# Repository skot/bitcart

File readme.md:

## The Bitcart

The bitcart is an open source controlboard for Bitmain Antminers. It runs off a RPi CM4 and the design is based around the [Raspberry Pi Compute Module 4 IO Board](https://www.raspberrypi.com/products/compute-module-4-io-board/)

If you are trying run a Bitcoin ASIC miner somewhere besides a datacenter, this is the controlboard for you.

**design is currently in alpha stage and untested!**

### Goals
- Initial support for Antminer S19J, S19K and S19XP series miners.
  - eventual support for S19, S17 and S9 legacy miners. 
- Fully open source hardware and firmware
- Runs the open source [esp-miner](http://github.com/skot/esp-miner) ported to linux.
  - miner FW modularized to allow for easy modification. Better utilize stranded energy! 
- IO options for customization
  - Ethernet
  - WiFi
  - Bluetooth
  - USB2
  - PCIe
  - RPi 40-pin header
- Built-in options for hashboard testing and repair

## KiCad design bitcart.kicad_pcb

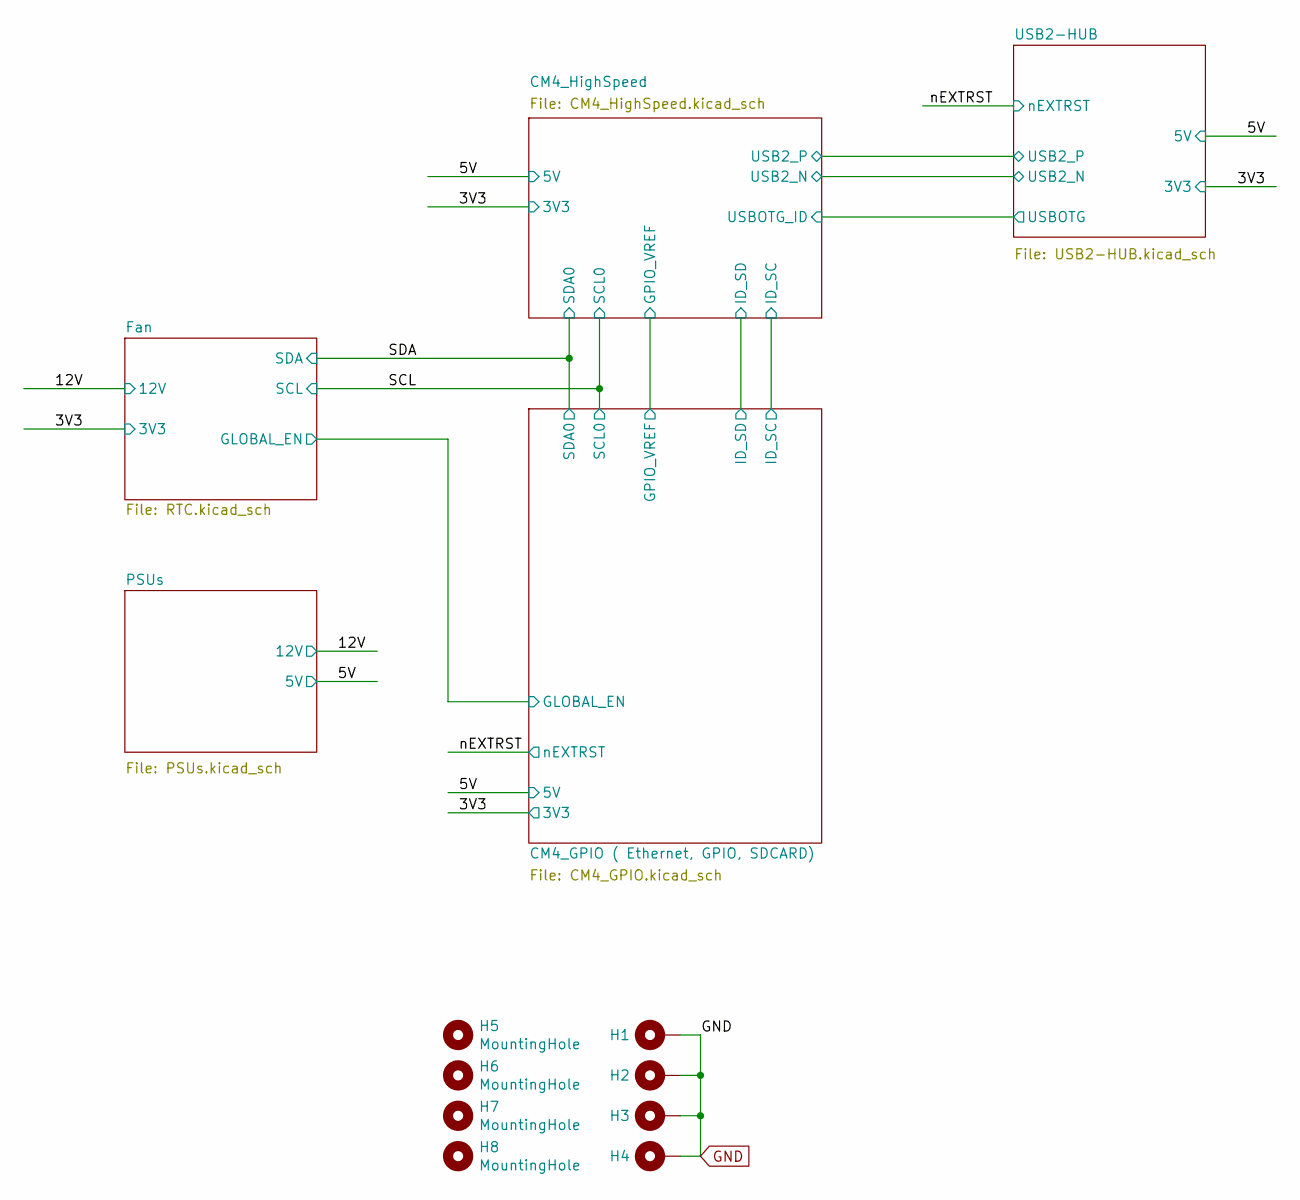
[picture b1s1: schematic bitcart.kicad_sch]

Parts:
H1, H2, H3, H4: MountingHole_Pad; MountingHole_3mm_Pad
H5, H6, H7, H8: MountingHole; MountingHole_2.7mm_M2.5; Part Description M2.5 mounting hole

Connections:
GND: H1.1, H2.1, H3.1, H4.1; also elsewhere on the board

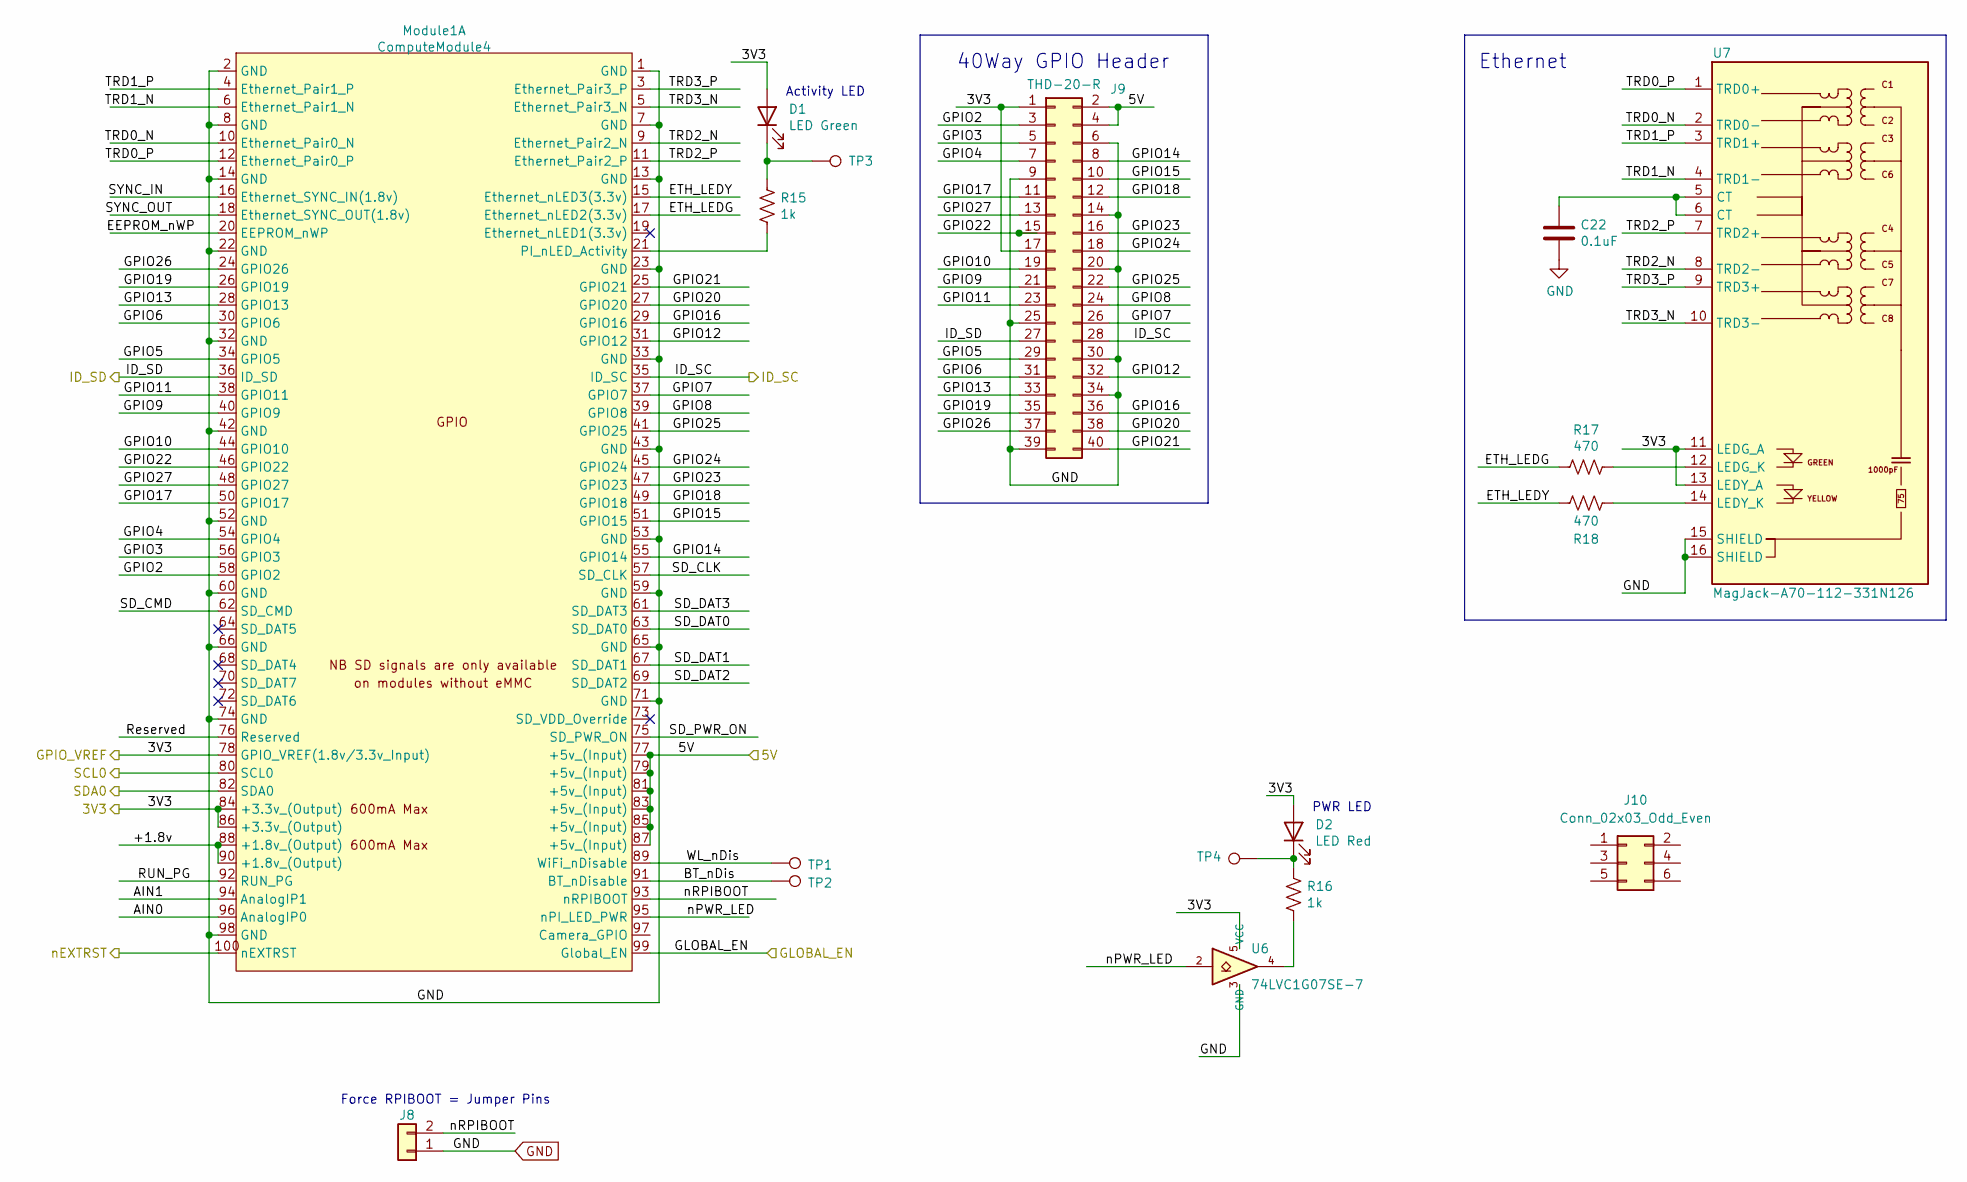
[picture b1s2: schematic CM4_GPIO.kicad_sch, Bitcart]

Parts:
C22: 0.1uF; C_0402_1005Metric; PARTNO KGM05AR71C104KH
D1: LED Green; LED_0603_1608Metric; PARTNO LTST-S270KGKT
D2: LED Red; LED_0603_1608Metric; Part Description Red 620nm LED Indication - Discrete 2.2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
J8: Conn_01x02; PinHeader_1x02_P2.54mm_Vertical
J9: THD-20-R; PinHeader_2x20_P2.54mm_Vertical; Part Description PinHeader_2x20_P2.54mm_Vertical
J10: Conn_02x03_Odd_Even; CONN-TH_6P-P2.00_PHD-2X3A
Module1: ComputeModule4; Raspberry-Pi-4-Compute-Module; PARTNO DF40C-100DS-0.4V(58)
R15, R16: 1k; R_0402_1005Metric; Part Description Resistor 1K M1005 1% 63mW
R17, R18: 470; R_0402_1005Metric; Part Description Resistor 470R M1005 1% 63mW
TP1, TP2, TP3, TP4: TestPoint; TestPoint_Pad_D1.5mm
U6: 74LVC1G07SE-7; SOT-353_SC-70-5; PARTNO 74LVC1G07GW,125
U7: MagJack-A70-112-331N126; ARJM11D7-502-AB-EW2_ABR; Part Description Gigabit Ethernet Magjack

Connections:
/3V3: D1.2 (A), D2.2 (A), J9.1, J9.17, Module1.78 (GPIO_VREF(1.8v/3.3v_Input)), Module1.84 (+3.3v_(Output)), Module1.86 (+3.3v_(Output)), U6.5 (VCC), U7.11 (LEDG_A), U7.13 (LEDY_A); also elsewhere on the board
/5V: J9.2, J9.4, Module1.77 (+5v_(Input)), Module1.79 (+5v_(Input)), Module1.81 (+5v_(Input)), Module1.83 (+5v_(Input)), Module1.85 (+5v_(Input)), Module1.87 (+5v_(Input)); also elsewhere on the board
/CM4_GPIO ( Ethernet, GPIO, SDCARD)/+1.8v: Module1.88 (+1.8v_(Output)), Module1.90 (+1.8v_(Output))
/CM4_GPIO ( Ethernet, GPIO, SDCARD)/AIN0: Module1.96 (AnalogIP0)
/CM4_GPIO ( Ethernet, GPIO, SDCARD)/AIN1: Module1.94 (AnalogIP1)
/CM4_GPIO ( Ethernet, GPIO, SDCARD)/BT_nDis: Module1.91 (BT_nDisable), TP2.1
/CM4_GPIO ( Ethernet, GPIO, SDCARD)/EEPROM_nWP: Module1.20 (EEPROM_nWP)
/CM4_GPIO ( Ethernet, GPIO, SDCARD)/ETH_LEDG: Module1.17 (Ethernet_nLED2(3.3v)), R17.2
/CM4_GPIO ( Ethernet, GPIO, SDCARD)/ETH_LEDY: Module1.15 (Ethernet_nLED3(3.3v)), R18.2
/CM4_GPIO ( Ethernet, GPIO, SDCARD)/GLOBAL_EN: Module1.99 (Global_EN)
/CM4_GPIO ( Ethernet, GPIO, SDCARD)/GPIO2: J9.3, Module1.58 (GPIO2)
/CM4_GPIO ( Ethernet, GPIO, SDCARD)/GPIO3: J9.5, Module1.56 (GPIO3)
/CM4_GPIO ( Ethernet, GPIO, SDCARD)/GPIO4: J9.7, Module1.54 (GPIO4)
/CM4_GPIO ( Ethernet, GPIO, SDCARD)/GPIO5: J9.29, Module1.34 (GPIO5)
/CM4_GPIO ( Ethernet, GPIO, SDCARD)/GPIO6: J9.31, Module1.30 (GPIO6)
/CM4_GPIO ( Ethernet, GPIO, SDCARD)/GPIO7: J9.26, Module1.37 (GPIO7)
/CM4_GPIO ( Ethernet, GPIO, SDCARD)/GPIO8: J9.24, Module1.39 (GPIO8)
/CM4_GPIO ( Ethernet, GPIO, SDCARD)/GPIO9: J9.21, Module1.40 (GPIO9)
/CM4_GPIO ( Ethernet, GPIO, SDCARD)/GPIO10: J9.19, Module1.44 (GPIO10)
/CM4_GPIO ( Ethernet, GPIO, SDCARD)/GPIO11: J9.23, Module1.38 (GPIO11)
/CM4_GPIO ( Ethernet, GPIO, SDCARD)/GPIO12: J9.32, Module1.31 (GPIO12)
/CM4_GPIO ( Ethernet, GPIO, SDCARD)/GPIO13: J9.33, Module1.28 (GPIO13)
/CM4_GPIO ( Ethernet, GPIO, SDCARD)/GPIO14: J9.8, Module1.55 (GPIO14)
/CM4_GPIO ( Ethernet, GPIO, SDCARD)/GPIO15: J9.10, Module1.51 (GPIO15)
/CM4_GPIO ( Ethernet, GPIO, SDCARD)/GPIO16: J9.36, Module1.29 (GPIO16)
/CM4_GPIO ( Ethernet, GPIO, SDCARD)/GPIO17: J9.11, Module1.50 (GPIO17)
/CM4_GPIO ( Ethernet, GPIO, SDCARD)/GPIO18: J9.12, Module1.49 (GPIO18)
/CM4_GPIO ( Ethernet, GPIO, SDCARD)/GPIO19: J9.35, Module1.26 (GPIO19)
/CM4_GPIO ( Ethernet, GPIO, SDCARD)/GPIO20: J9.38, Module1.27 (GPIO20)
/CM4_GPIO ( Ethernet, GPIO, SDCARD)/GPIO21: J9.40, Module1.25 (GPIO21)
/CM4_GPIO ( Ethernet, GPIO, SDCARD)/GPIO22: J9.15, Module1.46 (GPIO22)
/CM4_GPIO ( Ethernet, GPIO, SDCARD)/GPIO23: J9.16, Module1.47 (GPIO23)
/CM4_GPIO ( Ethernet, GPIO, SDCARD)/GPIO24: J9.18, Module1.45 (GPIO24)
/CM4_GPIO ( Ethernet, GPIO, SDCARD)/GPIO25: J9.22, Module1.41 (GPIO25)
/CM4_GPIO ( Ethernet, GPIO, SDCARD)/GPIO26: J9.37, Module1.24 (GPIO26)
/CM4_GPIO ( Ethernet, GPIO, SDCARD)/GPIO27: J9.13, Module1.48 (GPIO27)
/CM4_GPIO ( Ethernet, GPIO, SDCARD)/ID_SC: J9.28, Module1.35 (ID_SC); also elsewhere on the board
/CM4_GPIO ( Ethernet, GPIO, SDCARD)/ID_SD: J9.27, Module1.36 (ID_SD); also elsewhere on the board
/CM4_GPIO ( Ethernet, GPIO, SDCARD)/RUN_PG: Module1.92 (RUN_PG)
/CM4_GPIO ( Ethernet, GPIO, SDCARD)/Reserved: Module1.76 (Reserved)
/CM4_GPIO ( Ethernet, GPIO, SDCARD)/SD_CLK: Module1.57 (SD_CLK)
/CM4_GPIO ( Ethernet, GPIO, SDCARD)/SD_CMD: Module1.62 (SD_CMD)
/CM4_GPIO ( Ethernet, GPIO, SDCARD)/SD_DAT0: Module1.63 (SD_DAT0)
/CM4_GPIO ( Ethernet, GPIO, SDCARD)/SD_DAT1: Module1.67 (SD_DAT1)
/CM4_GPIO ( Ethernet, GPIO, SDCARD)/SD_DAT2: Module1.69 (SD_DAT2)
/CM4_GPIO ( Ethernet, GPIO, SDCARD)/SD_DAT3: Module1.61 (SD_DAT3)
/CM4_GPIO ( Ethernet, GPIO, SDCARD)/SD_PWR_ON: Module1.75 (SD_PWR_ON)
/CM4_GPIO ( Ethernet, GPIO, SDCARD)/SYNC_IN: Module1.16 (Ethernet_SYNC_IN(1.8v))
/CM4_GPIO ( Ethernet, GPIO, SDCARD)/SYNC_OUT: Module1.18 (Ethernet_SYNC_OUT(1.8v))
/CM4_GPIO ( Ethernet, GPIO, SDCARD)/TRD0_N: Module1.10 (Ethernet_Pair0_N), U7.2 (TRD0-)
/CM4_GPIO ( Ethernet, GPIO, SDCARD)/TRD0_P: Module1.12 (Ethernet_Pair0_P), U7.1 (TRD0+)
/CM4_GPIO ( Ethernet, GPIO, SDCARD)/TRD1_N: Module1.6 (Ethernet_Pair1_N), U7.4 (TRD1-)
/CM4_GPIO ( Ethernet, GPIO, SDCARD)/TRD1_P: Module1.4 (Ethernet_Pair1_P), U7.3 (TRD1+)
/CM4_GPIO ( Ethernet, GPIO, SDCARD)/TRD2_N: Module1.9 (Ethernet_Pair2_N), U7.8 (TRD2-)
/CM4_GPIO ( Ethernet, GPIO, SDCARD)/TRD2_P: Module1.11 (Ethernet_Pair2_P), U7.7 (TRD2+)
/CM4_GPIO ( Ethernet, GPIO, SDCARD)/TRD3_N: Module1.5 (Ethernet_Pair3_N), U7.10 (TRD3-)
/CM4_GPIO ( Ethernet, GPIO, SDCARD)/TRD3_P: Module1.3 (Ethernet_Pair3_P), U7.9 (TRD3+)
/CM4_GPIO ( Ethernet, GPIO, SDCARD)/WL_nDis: Module1.89 (WiFi_nDisable), TP1.1
/CM4_GPIO ( Ethernet, GPIO, SDCARD)/nPWR_LED: Module1.95 (nPI_LED_PWR), U6.2
/CM4_GPIO ( Ethernet, GPIO, SDCARD)/nRPIBOOT: J8.2, Module1.93 (nRPIBOOT)
/SCL: Module1.80 (SCL0); also elsewhere on the board
/SDA: Module1.82 (SDA0); also elsewhere on the board
/nEXTRST: Module1.100 (nEXTRST); also elsewhere on the board
GND: C22.2, J8.1, J9.6, J9.9, J9.14, J9.20, J9.25, J9.30, J9.34, J9.39, Module1.1 (GND), Module1.2 (GND), Module1.7 (GND), Module1.8 (GND), Module1.13 (GND), Module1.14 (GND), Module1.22 (GND), Module1.23 (GND), Module1.32 (GND), Module1.33 (GND), Module1.42 (GND), Module1.43 (GND), Module1.52 (GND), Module1.53 (GND), Module1.59 (GND), Module1.60 (GND), Module1.65 (GND), Module1.66 (GND), Module1.71 (GND), Module1.74 (GND), Module1.98 (GND), U6.3 (GND), U7.15 (SHIELD), U7.16 (SHIELD); also elsewhere on the board
unnamed: C22.1, U7.5 (CT), U7.6 (CT)
unnamed: D1.1 (K), R15.1, TP3.1
unnamed: D2.1 (K), R16.1, TP4.1
unnamed: Module1.21 (PI_nLED_Activity), R15.2
unnamed: R16.2, U6.4
unnamed: R17.1, U7.12 (LEDG_K)
unnamed: R18.1, U7.14 (LEDY_K)

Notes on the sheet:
PWR LED
40Way GPIO Header
Ethernet
Activity LED
Force RPIBOOT = Jumper Pins

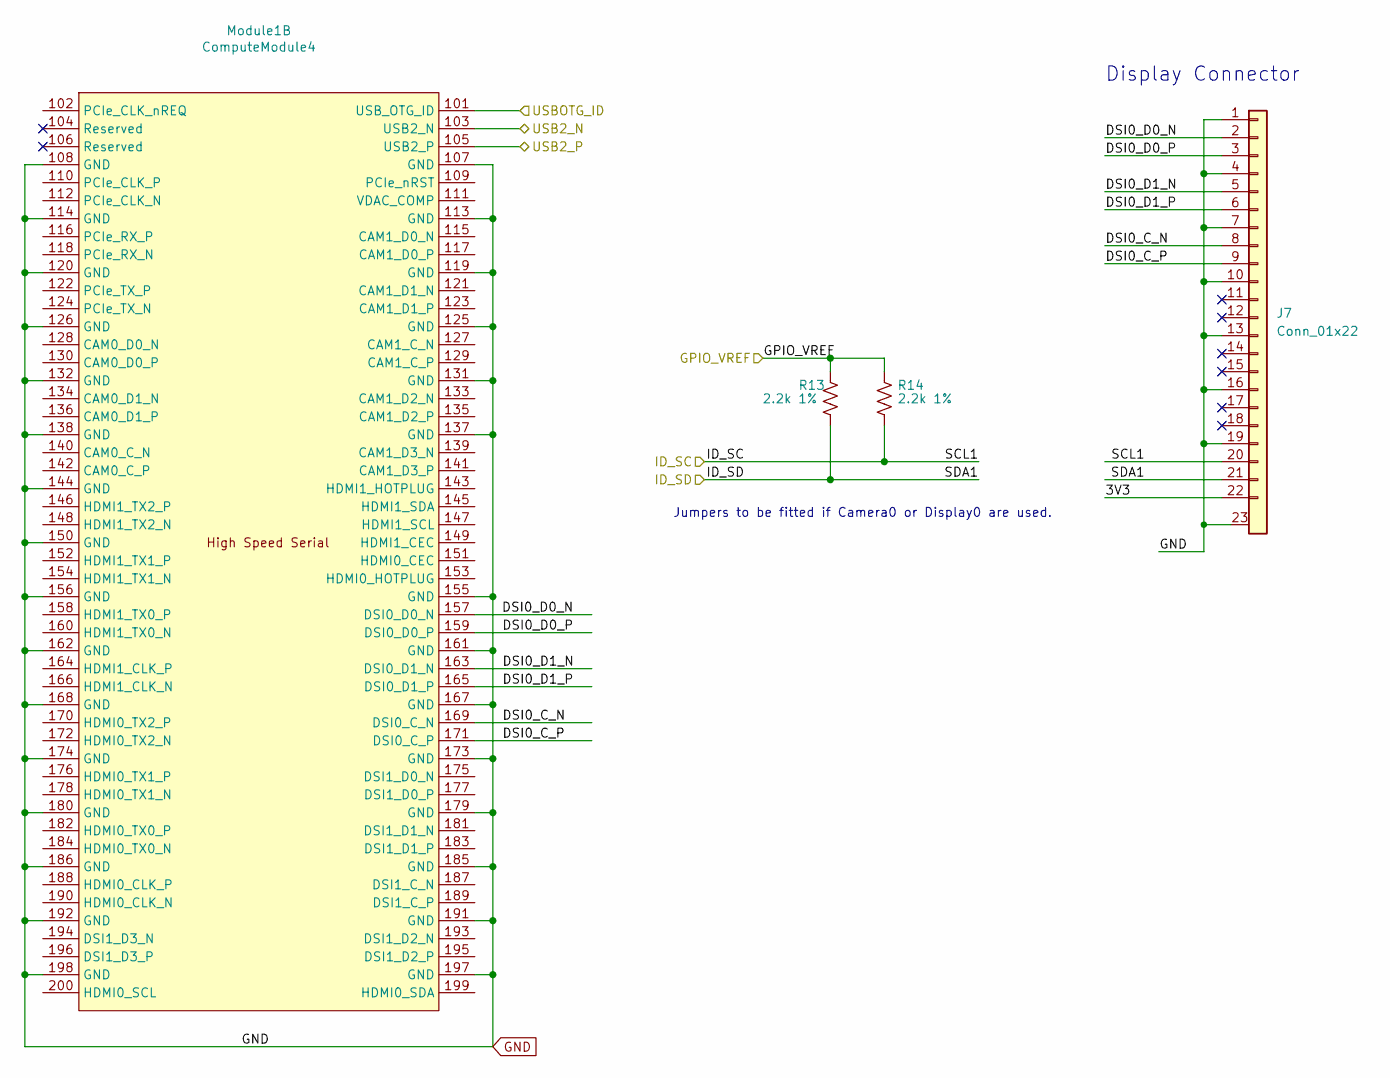
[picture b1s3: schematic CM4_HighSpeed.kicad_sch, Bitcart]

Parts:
J7: Conn_01x22; CON22_1X22_DUTB_HRS_HIR; PARTNO FH12-22S-0.5SVA(54)
Module1: ComputeModule4; Raspberry-Pi-4-Compute-Module; PARTNO DF40C-100DS-0.4V(58)
R13, R14: 2.2k 1%; R_0402_1005Metric; PARTNO RC0402FR-072K2L

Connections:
/3V3: R13.1, R14.1; also elsewhere on the board
/CM4_GPIO ( Ethernet, GPIO, SDCARD)/ID_SC: J7.20, R14.2; also elsewhere on the board
/CM4_GPIO ( Ethernet, GPIO, SDCARD)/ID_SD: J7.21, R13.2; also elsewhere on the board
/CM4_HighSpeed/3V3: J7.22
/CM4_HighSpeed/DSI0_C_N: J7.8, Module1.169 (DSI0_C_N)
/CM4_HighSpeed/DSI0_C_P: J7.9, Module1.171 (DSI0_C_P)
/CM4_HighSpeed/DSI0_D0_N: J7.2, Module1.157 (DSI0_D0_N)
/CM4_HighSpeed/DSI0_D0_P: J7.3, Module1.159 (DSI0_D0_P)
/CM4_HighSpeed/DSI0_D1_N: J7.5, Module1.163 (DSI0_D1_N)
/CM4_HighSpeed/DSI0_D1_P: J7.6, Module1.165 (DSI0_D1_P)
/CM4_HighSpeed/USB2_N: Module1.103 (USB2_N); also elsewhere on the board
/CM4_HighSpeed/USB2_P: Module1.105 (USB2_P); also elsewhere on the board
/CM4_HighSpeed/USBOTG_ID: Module1.101 (USB_OTG_ID); also elsewhere on the board
GND: J7.1, J7.4, J7.7, J7.10, J7.13, J7.16, J7.19, J7.23, J7.24, J7.25, J7.26, Module1.107 (GND), Module1.108 (GND), Module1.113 (GND), Module1.114 (GND), Module1.119 (GND), Module1.120 (GND), Module1.125 (GND), Module1.126 (GND), Module1.131 (GND), Module1.132 (GND), Module1.137 (GND), Module1.138 (GND), Module1.144 (GND), Module1.150 (GND), Module1.155 (GND), Module1.156 (GND), Module1.161 (GND), Module1.162 (GND), Module1.167 (GND), Module1.168 (GND), Module1.173 (GND), Module1.174 (GND), Module1.179 (GND), Module1.180 (GND), Module1.185 (GND), Module1.186 (GND), Module1.191 (GND), Module1.192 (GND), Module1.197 (GND), Module1.198 (GND); also elsewhere on the board

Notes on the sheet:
Jumpers to be fitted if Camera0 or Display0 are used.
Display Connector

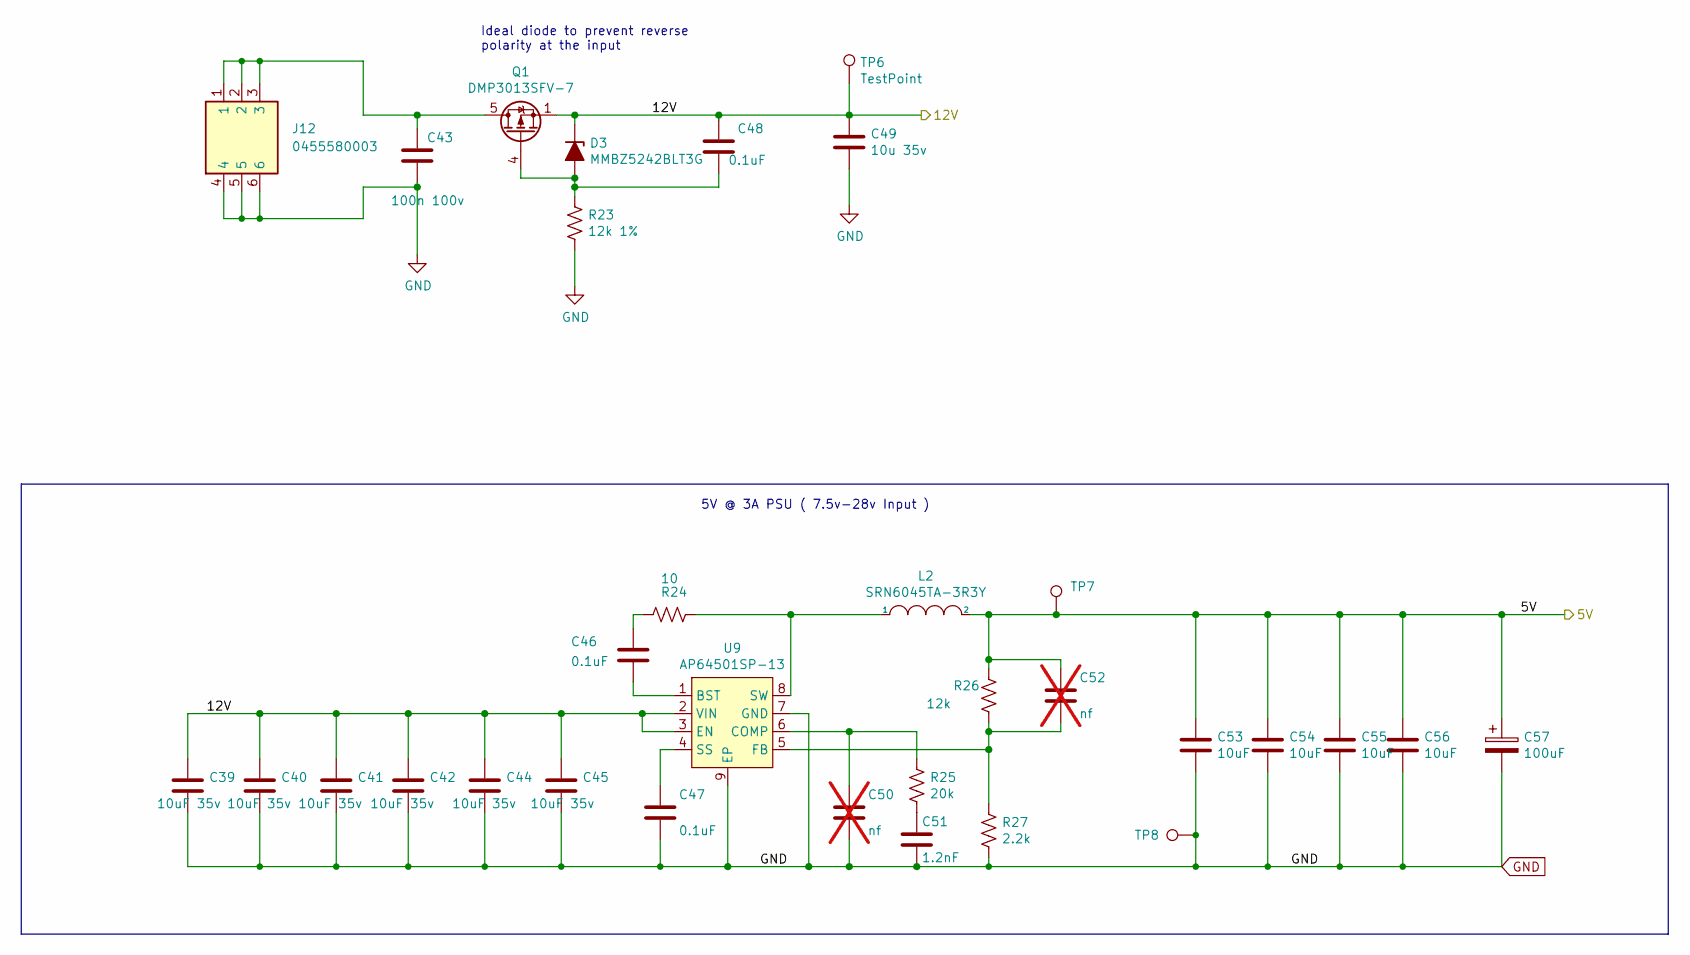
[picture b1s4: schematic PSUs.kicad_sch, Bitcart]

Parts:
C39, C40, C41, C42, C44, C45: 10uF 35v; C_0805_2012Metric; Part Description 10uF 10% or 20% 35V Ceramic Capacitor X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
C43: 100n 100v; C_0402_1005Metric; Part Description 0.1uF 10% 100V Ceramic Capacitor X5R 04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
C46, C47, C48: 0.1uF; C_0402_1005Metric; PARTNO KGM05AR71C104KH
C49: 10u 35v; C_0805_2012Metric; Part Description 10uF 10% or 20% 35V Ceramic Capacitor X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
C50: nf; C_0402_1005Metric; not fitted
C51: 1.2nF; C_0402_1005Metric; Part Description 1200pF 10% 10V Ceramic Capacitor X5R 04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
C52: nf; C_0402_1005Metric; Part Description 220 pF, 50 V, 0402 [1005 Metric], ± 5%,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; not fitted
C53, C54, C55, C56: 10uF; C_0805_2012Metric; Part Description 10uF 10% 10V Ceramic Capacitor X7R 0805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
C57: 100uF; CP_EIA-7343-31_Kemet-D; Part Description Capacitor, SP-Cap, 100u, 6.3V, 15mR ESR
D3: MMBZ5242BLT3G; D_SOT-23_ANK; PARTNO MMBZ5242BLT3G
J12: 0455580003; PARTNO 0455580003
L2: SRN6045TA-3R3Y; L_Bourns_SRN6045TA
Q1: DMP3013SFV-7; Diodes_PowerDI3333-8; PARTNO DMP3013SFV-7
R23: 12k 1%; R_0402_1005Metric; Part Description Resistor 12K M1005 1% 63mW
R24: 10; R_0402_1005Metric; Part Description Resistor 10R M1005 1% 63mW
R25: 20k; R_0402_1005Metric; Part Description Resistor 20K M1005 1% 63mW
R26: 12k; R_0402_1005Metric; Part Description Resistor 12K M1005 1% 63mW
R27: 2.2k; R_0402_1005Metric; Part Description Resistor 2.2K M1005 1% 63mW
TP6, TP7, TP8: TestPoint; TestPoint_Pad_D1.5mm
U9: AP64501SP-13; SOIC-8-1EP_3.9x4.9mm_P1.27mm_EP2.95x4.9mm_Mask2.71x3.4mm_Th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; PARTNO AP64501SP-13

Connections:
/5V: C52.1, C53.1, C54.1, C55.1, C56.1, C57.1, L2.2, R26.1, TP7.1; also elsewhere on the board
/12V: C39.1, C40.1, C41.1, C42.1, C44.1, C45.1, C48.1, C49.1, D3.3 (K), Q1.1 (S), Q1.2 (S), Q1.3 (S), TP6.1, U9.2 (VIN), U9.3 (EN); also elsewhere on the board
GND: C39.2, C40.2, C41.2, C42.2, C43.2, C44.2, C45.2, C47.2, C49.2, C50.2, C51.2, C53.2, C54.2, C55.2, C56.2, C57.2, J12.4, J12.5, J12.6, R23.2, R27.2, TP8.1, U9.7 (GND), U9.9 (EP); also elsewhere on the board
unnamed: C46.1, R24.2
unnamed: C51.1, R25.2
unnamed: C48.2, D3.1 (A), Q1.4 (G), R23.1
unnamed: C43.1, J12.1, J12.2, J12.3, Q1.5 (D)
unnamed: C46.2, U9.1 (BST)
unnamed: C50.1, R25.1, U9.6 (COMP)
unnamed: C52.2, R26.2, R27.1, U9.5 (FB)
unnamed: C47.1, U9.4 (SS)
unnamed: L2.1, R24.1, U9.8 (SW)

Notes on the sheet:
Ideal diode to prevent reverse polarity at the input
5V @ 3A PSU ( 7.5v-28v Input )

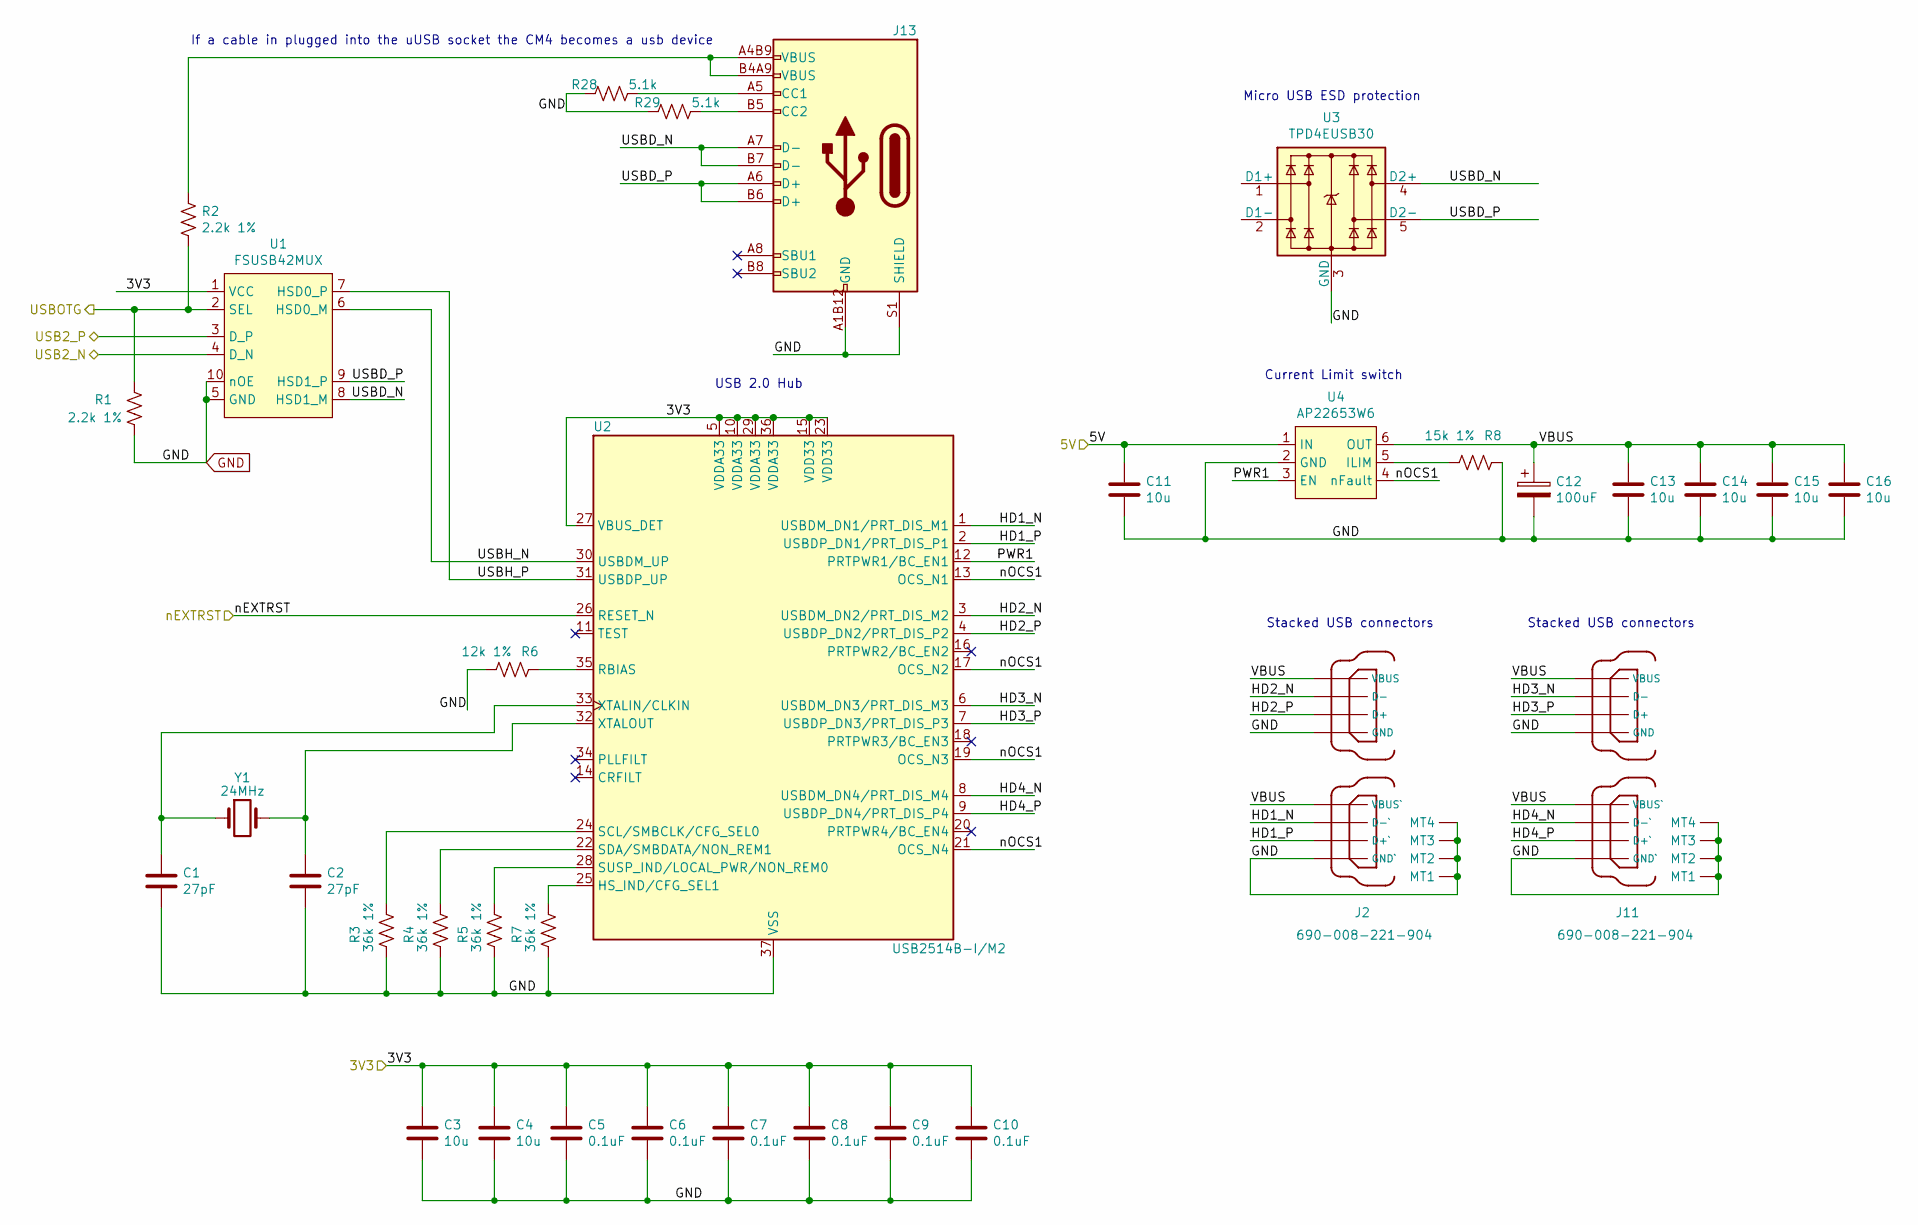
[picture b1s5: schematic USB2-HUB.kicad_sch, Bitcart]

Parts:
C1, C2: 27pF; C_0402_1005Metric; Part Description 27pF 5% 50V Ceramic Capacitor C0G, NP0 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
C3, C4, C11, C13, C14, C15, C16: 10u; C_0805_2012Metric; Part Description 10uF 10% 10V Ceramic Capacitor X7R 0805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
C5, C6, C7, C8, C9, C10: 0.1uF; C_0402_1005Metric; PARTNO KGM05AR71C104KH
C12: 100uF; CP_EIA-7343-31_Kemet-D; Part Description Capacitor, SP-Cap, 100u, 6.3V, 15mR ESR
J2, J11: 690-008-221-904; MOLEX_USB_67298-4090; PARTNO 0672984090
J13: USB_C_Receptacle_USB2.0; USB_C_Receptacle_GCT_USB4105-xx-A_16P_TopMnt_Horizontal; PARTNO USB4105-GF-A; LCSC Part C2988369
R1, R2: 2.2k 1%; R_0402_1005Metric; Part Description Resistor 2.2K M1005 1% 63mW
R3, R4, R5, R7: 36k 1%; R_0402_1005Metric; Part Description Resistor 36K M1005 1% 63mW
R6: 12k 1%; R_0402_1005Metric; Part Description Resistor 12K M1005 1% 63mW
R8: 15k 1%; R_0402_1005Metric; Part Description Resistor 15K M1005 1% 63mW
R28, R29: 5.1k; R_0402_1005Metric; PARTNO RMCF0402JT5K10; LCSC Part C25905
U1: FSUSB42MUX; MSOP-10_3x3mm_P0.5mm; PARTNO FSUSB42MUX
U2: USB2514B-I/M2; QFN-36-1EP_6x6mm_P0.5mm_EP3.7x3.7mm; PARTNO USB2514B-I/M2
U3: TPD4EUSB30; USON-10_2.5x1.0mm_P0.5mm; PARTNO TPD4EUSB30DQAR
U4: AP22653W6; SOT-23-6; PARTNO AP2553W6-7
Y1: 24MHz; CRYSTAL_ABM8G_ABR; PARTNO ABM8G-24.000MHZ-18-D2Y-T

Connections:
/3V3: C3.1, C4.1, C5.1, C6.1, C7.1, C8.1, C9.1, C10.1, U1.1 (VCC), U2.5 (VDDA33), U2.10 (VDDA33), U2.15 (VDD33), U2.23 (VDD33), U2.27 (VBUS_DET), U2.29 (VDDA33), U2.36 (VDDA33); also elsewhere on the board
/5V: C11.1, U4.1 (IN); also elsewhere on the board
/CM4_HighSpeed/USB2_N: U1.4 (D_N); also elsewhere on the board
/CM4_HighSpeed/USB2_P: U1.3 (D_P); also elsewhere on the board
/CM4_HighSpeed/USBOTG_ID: R1.1, R2.2, U1.2 (SEL); also elsewhere on the board
/USB2-HUB/HD1_N: J2.2 (D-`), U2.1 (USBDM_DN1/PRT_DIS_M1)
/USB2-HUB/HD1_P: J2.3 (D+`), U2.2 (USBDP_DN1/PRT_DIS_P1)
/USB2-HUB/HD2_N: J2.6 (D-), U2.3 (USBDM_DN2/PRT_DIS_M2)
/USB2-HUB/HD2_P: J2.7 (D+), U2.4 (USBDP_DN2/PRT_DIS_P2)
/USB2-HUB/HD3_N: J11.6 (D-), U2.6 (USBDM_DN3/PRT_DIS_M3)
/USB2-HUB/HD3_P: J11.7 (D+), U2.7 (USBDP_DN3/PRT_DIS_P3)
/USB2-HUB/HD4_N: J11.2 (D-`), U2.8 (USBDM_DN4/PRT_DIS_M4)
/USB2-HUB/HD4_P: J11.3 (D+`), U2.9 (USBDP_DN4/PRT_DIS_P4)
/USB2-HUB/PWR1: U2.12 (PRTPWR1/BC_EN1), U4.3 (EN)
/USB2-HUB/USBD_N: J13.A7 (D-), J13.B7 (D-), U1.8 (HSD1_M), U3.4 (D2+), U3.7
/USB2-HUB/USBD_P: J13.A6 (D+), J13.B6 (D+), U1.9 (HSD1_P), U3.5 (D2-), U3.6
/USB2-HUB/USBH_N: U1.6 (HSD0_M), U2.30 (USBDM_UP)
/USB2-HUB/USBH_P: U1.7 (HSD0_P), U2.31 (USBDP_UP)
/USB2-HUB/VBUS: C12.1, C13.1, C14.1, C15.1, C16.1, J2.1 (VBUS`), J2.5 (VBUS), J11.1 (VBUS`), J11.5 (VBUS), U4.6 (OUT)
/USB2-HUB/nOCS1: U2.13 (OCS_N1), U2.17 (OCS_N2), U2.19 (OCS_N3), U2.21 (OCS_N4), U4.4 (nFault)
/nEXTRST: U2.26 (RESET_N); also elsewhere on the board
GND: C1.2, C2.2, C3.2, C4.2, C5.2, C6.2, C7.2, C8.2, C9.2, C10.2, C11.2, C12.2, C13.2, C14.2, C15.2, C16.2, J2.4 (GND`), J2.8 (GND), J2.MT1, J2.MT2, J2.MT3, J2.MT4, J11.4 (GND`), J11.8 (GND), J11.MT1, J11.MT2, J11.MT3, J11.MT4, J13.A1B12 (GND), J13.B1A12 (GND), J13.S1 (SHIELD), R1.2, R3.2, R4.2, R5.2, R6.1, R7.2, R8.2, R28.1, R29.1, U1.5 (GND), U1.10 (nOE), U2.37 (VSS), U3.3 (GND), U3.8 (GND), U4.2 (GND); also elsewhere on the board
unnamed: J13.A5 (CC1), R28.2
unnamed: J13.B5 (CC2), R29.2
unnamed: J13.A4B9 (VBUS), J13.B4A9 (VBUS), R2.1
unnamed: R7.1, U2.25 (HS_IND/CFG_SEL1)
unnamed: R6.2, U2.35 (RBIAS)
unnamed: R3.1, U2.24 (SCL/SMBCLK/CFG_SEL0)
unnamed: R4.1, U2.22 (SDA/SMBDATA/NON_REM1)
unnamed: R5.1, U2.28 (SUSP_IND/LOCAL_PWR/NON_REM0)
unnamed: C1.1, U2.33 (XTALIN/CLKIN), Y1.1
unnamed: C2.1, U2.32 (XTALOUT), Y1.3
unnamed: U3.1 (D1+), U3.10
unnamed: U3.2 (D1-), U3.9
unnamed: R8.1, U4.5 (ILIM)

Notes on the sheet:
Current Limit switch
Stacked USB connectors
USB 2.0 Hub
If a cable in plugged into the uUSB socket the CM4 becomes a usb device
Micro USB ESD protection

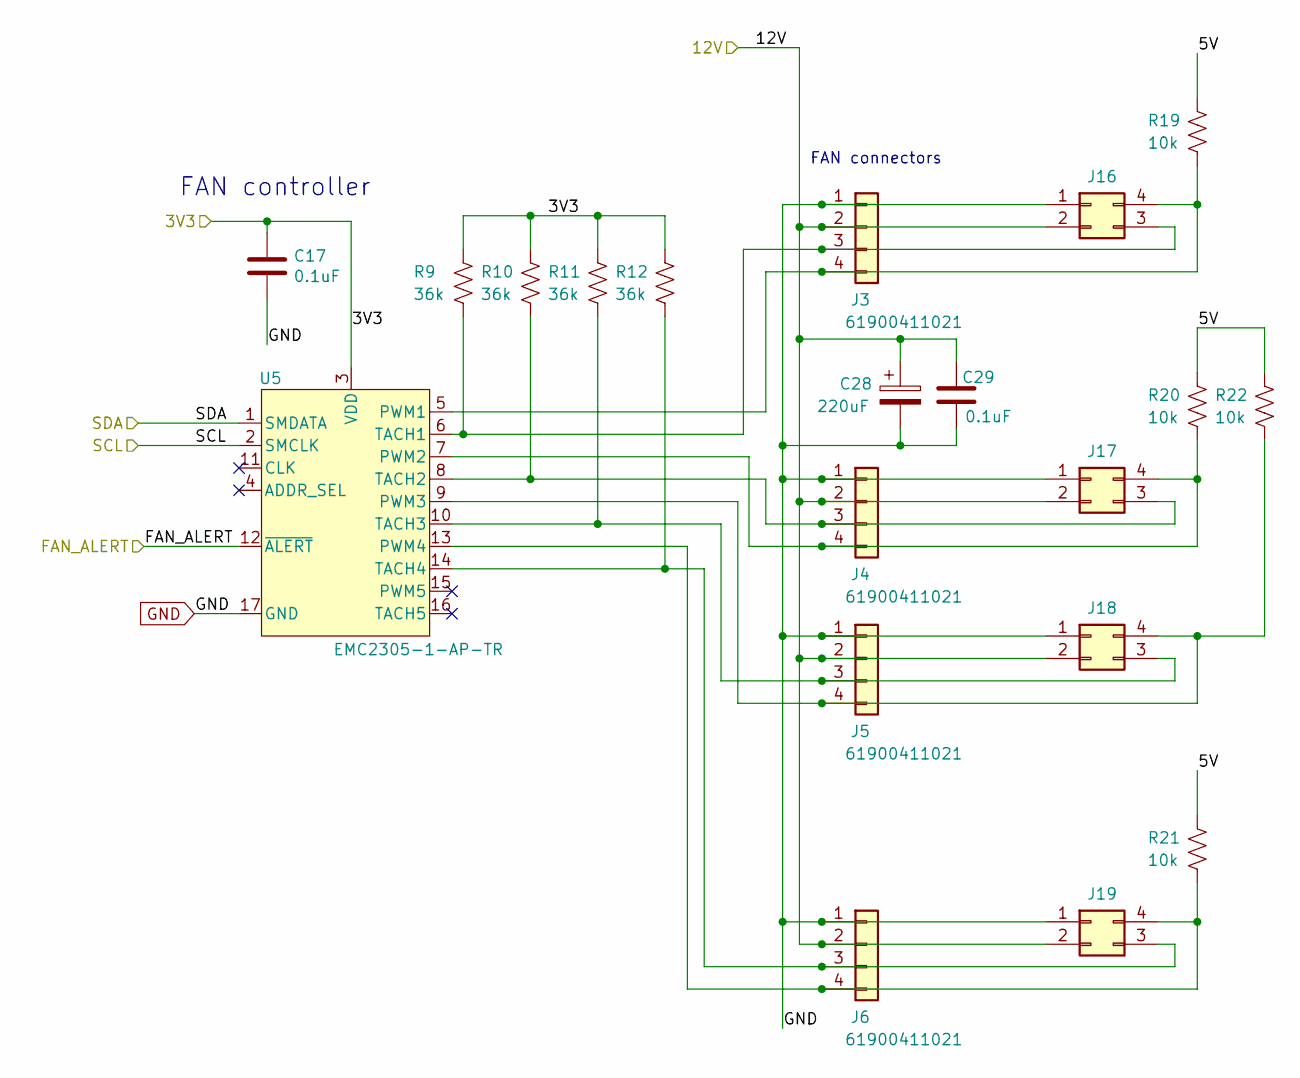
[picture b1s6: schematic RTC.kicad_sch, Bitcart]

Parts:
C17: 0.1uF; C_0402_1005Metric; PARTNO KGM05AR71C104KH
C28: 220uF; CP_Elec_6.3x7.7; PARTNO 865080345012
C29: 0.1uF; C_0402_1005Metric; PARTNO 0402X104K100CT
J3, J4, J5, J6: 61900411021; CONN_61900411021_WRE; PARTNO 61900411021
J16, J17, J18, J19: 0353180420; MOLEX_353180420; PARTNO 0353180420
R9, R10, R11, R12: 36k; R_0402_1005Metric; PARTNO CR0402-FX-3602GLF
R19, R20, R21, R22: 10k; R_0402_1005Metric
U5: EMC2305-1-AP-TR; QFN16_4x4MC_MCH

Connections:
/3V3: C17.1, R9.1, R10.1, R11.1, R12.1, U5.3 (VDD); also elsewhere on the board
/12V: J3.2, J4.2, J5.2, J6.2, J16.2, J17.2, J18.2, J19.2; also elsewhere on the board
/Fan/5V: R19.1, R20.1, R21.1, R22.1
/Fan/FAN_ALERT: U5.12 (~ALERT)
/SCL: U5.2 (SMCLK); also elsewhere on the board
/SDA: U5.1 (SMDATA); also elsewhere on the board
GND: C17.2, J3.1, J4.1, J5.1, J6.1, J16.1, J17.1, J18.1, J19.1, U5.17 (GND); also elsewhere on the board
unnamed: J3.3, J16.3, R9.2, U5.6 (TACH1)
unnamed: J3.4, J16.4, R19.2, U5.5 (PWM1)
unnamed: J4.3, J17.3, R10.2, U5.8 (TACH2)
unnamed: J4.4, J17.4, R20.2, U5.7 (PWM2)
unnamed: J5.3, J18.3, R11.2, U5.10 (TACH3)
unnamed: J5.4, J18.4, R22.2, U5.9 (PWM3)
unnamed: J6.3, J19.3, R12.2, U5.14 (TACH4)
unnamed: J6.4, J19.4, R21.2, U5.13 (PWM4)

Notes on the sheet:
FAN controller
FAN connectors
